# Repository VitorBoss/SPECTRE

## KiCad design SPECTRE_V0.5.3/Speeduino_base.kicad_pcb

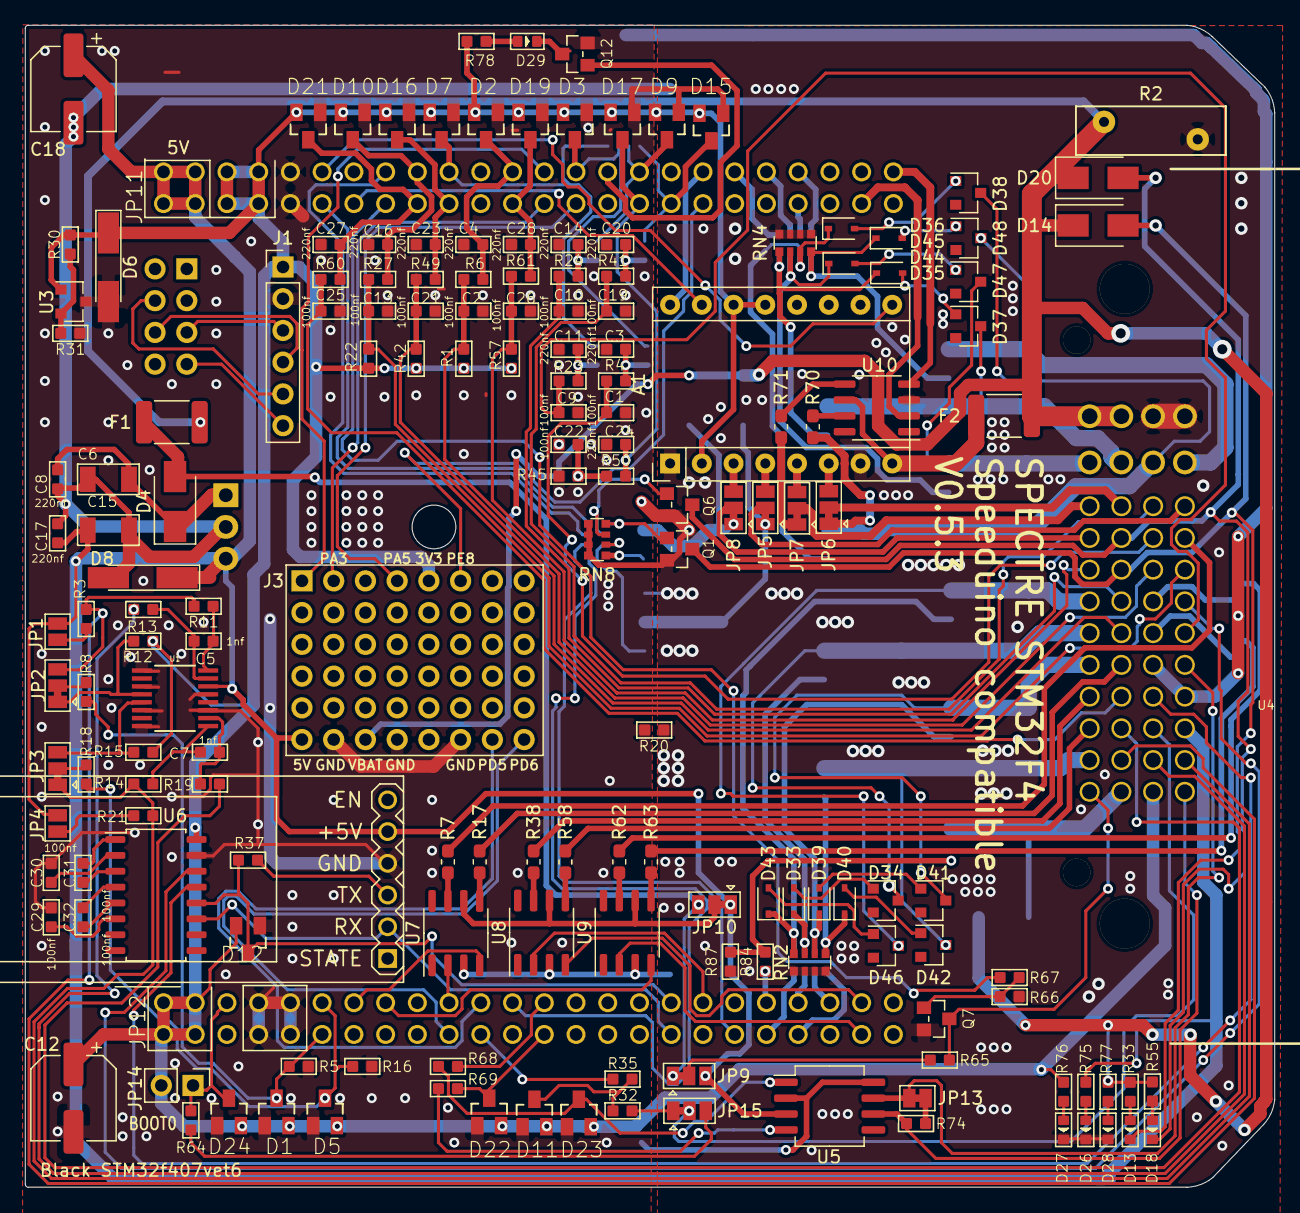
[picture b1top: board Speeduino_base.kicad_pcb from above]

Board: 2 copper layers, 100.0 x 93.0 mm, 197 parts (0 on the bottom side), 180 nets.

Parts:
A1: Pololu_Breakout_DRV8825; Pololu_Breakout-16_15.2x20.3mm
C1, C2, C9, C10, C13, C19, C21, C22, C25, C26, C29, C30, C31, C32: 100nf; C0603
C3, C4, C8, C11, C14, C16, C17, C20, C23, C24, C27, C28: 220nf; C0603
C5, C7: 1nf; C0603
C6, C15: 10uf; C1206
C12, C18: 470uF 6.3V; CP_Elec_6.3x7.7
D1, D2, D3, D5, D7, D9, D10, D11, D12, D15, D16, D17, D19, D21, D22, D23, D24: BAT54S; SOT23
D4, D14, D20, D30, D31, D32: 1N4007; D_SMA
D6: Zener 3.6V; D_MiniMELF_Handsoldering
D8: Zener 5.1V; D_MiniMELF_Handsoldering
D13, D18, D26, D27, D28, D29: YEL; LED-0603
D33, D35, D36, D39, D40, D43, D44, D45: 1N4148WS; D_SOD-323
D34, D37, D38, D41, D42, D46, D47, D48: BZX84C39; D_SOT-23_ANK
F1, F2: PPTC 16V2A; R_1812_4532Metric_Pad1.30x3.40mm_HandSolder
J1: Conn_01x06_Male; PinHeader_1x06_P2.54mm_Vertical
J2: Conn_02x04_Odd_Even; PinHeader_2x04_P2.54mm_Vertical
J3: ProtoArea; Proto_area
JP1, JP4: Jumper_NO_Small; SolderJumper-2_P1.3mm_Open_Pad1.0x1.5mm
JP2, JP3, JP5, JP6, JP7, JP8, JP9, JP10, JP15, JP16, JP18: SolderJumper_3_Bridged12; SolderJumper-3_P1.3mm_Bridged12_Pad1.0x1.5mm
JP11, JP12: PINHD-2X24; 2X24
JP13: Jumper_NC_Small; SolderJumper-2_P1.3mm_Bridged_Pad1.0x1.5mm
JP14: Jumper_NO_Small; PinHeader_1x02_P2.54mm_Vertical
Q1, Q6, Q7, Q12: AO3400; SOT-23
Q10, Q11, Q13, Q14, Q15, Q16, Q17, Q18, Q19, Q20, Q21: BSP78; SOT223
R1, R22, R31, R42, R57: 2k49; R0603
R2: VARISTOR-18V; RV_Disc_D12mm_W3.9mm_P7.5mm
R3, R12, R15, R21, R32, R35, R65, R68, R69: 1k; R0603
R4, R6, R8, R18, R23, R24, R27, R33, R37, R41, R49, R50, R55, R60, R61, R64, R77: 470R; R0603
R5, R11, R13, R14, R16, R19: 10k; R0603
R7, R17, R38, R58, R62, R63, R70, R71: 10R; R_0603_1608Metric_Pad1.05x0.95mm_HandSolder
R9, R25, R28, R46: 4k7; R0603
R20: 0R0; R0603
R30: 1k8; R0603
R44: 33k; R0603
R45: 5k1; R0603
R66, R87: 10K; R0603
R67, R76, R78, R84: 100R; R0603
R74: 120R; R0603
R75: 220R; R0603
RN1, RN3, RN7: 100R; R_Array_Convex_4x0612
RN2, RN4, RN8: 10K; R_Array_Convex_4x0612
RN6: 9K1; R_Array_Convex_4x0612
U1: MAX9926UAEE+; 21-0055H_16
U2: LM78M05_TO220; TO-220-3_Horizontal_TabUp
U3: TL431DBZ; SOT-23
U4: molex_48pin; Molex_48
U5: TJA1050; SO-8_5.3x6.2mm_P1.27mm
U6: MAX3232; SOIC-16_4.55x10.3mm_P1.27mm
U7, U8, U9, U10: MIC4427; SO-8_3.9x4.9mm_P1.27mm
U$1: WIRELESS-BLUETOOTH-HC-05

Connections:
3.3V: A1.2, A1.13, A1.14, C12.1, D1.2, D2.2, D3.2, D5.2, D6.1, D7.2, D9.2, D10.2, D11.2, D12.2, D15.2, D16.2, D17.2, D19.2, D21.2, D22.2, D23.2, D24.2, J1.1, J3.5, JP11.5, JP11.6, JP11.7, JP11.8, JP12.1, JP12.2, JP12.3, JP12.4, JP14.2, R1.2, R12.2, R15.2, R22.2, R30.1, R42.2, R57.2, R76.2, R78.2, U3.1, U4.46, U6.16
5V: C15.2, C17.2, C18.1, D8.1, J3.41, JP1.2, JP4.2, JP9.3, JP10.1, JP11.1, JP11.2, JP11.3, JP11.4, R75.2, U1.14, U2.3, U4.37, U5.3, U$1.5
/BT_TX: R37.2, U$1.3
AIN_1: C2.2, R1.1, R6.1, U4.18
AIN_2: C1.2, R4.1, U4.14
AIN_3: C26.2, R57.1, R61.1, U4.20
BARO: C19.2, R41.1, U4.10
BME280_CS: J1.5, J2.4
BOOST-OUT: D30.2, Q16.2, Q16.4, U4.47
BOOT0: D24.3, JP12.5, JP14.1, R64.1
BOOT0_EXT: JP15.3, R64.2
CANH: JP13.2, U4.29, U5.7
CANL: R74.1, U4.45, U5.6
CLT: C21.2, R42.1, R49.1, U4.27
FAN: D18.-, D20.2, Q6.3, U4.15
FLEX_FUEL_IN: JP15.1, R32.2
FUEL_PUMP: D13.-, D14.2, Q1.3, U4.19
GND: C1.1, C2.1, C3.1, C4.1, C9.1, C10.1, C11.1, C12.2, C13.1, C14.1, C16.1, C19.1, C20.1, C21.1, C22.1, C23.1, C24.1, C25.1, C26.1, C27.1, C28.1, C29.2, C30.2, D1.1, D2.1, D3.1, D5.1, D6.2, D7.1, D9.1, D10.1, D11.1, D12.1, D15.1, D16.1, D17.1, D19.1, D21.1, D22.1, D23.1, D24.1, J1.2, J3.42, J3.44, J3.46, JP11.9, JP11.10, JP12.7, JP12.8, JP12.9, JP12.10, JP16.1, JP18.1, Q12.2, R5.2, R16.2, R20.1, R31.2, R45.1, RN6.1, RN6.2, RN6.3, RN6.4, U1.1, U1.3, U1.6, U1.8, U1.11, U1.13, U3.3, U4.30, U4.33, U5.2, U5.8, U6.15, U$1.4
IAT: C13.2, R22.1, R27.1, U4.17
IDLE1-OUT: D31.2, JP5.1, Q17.2, Q17.4
IDLE2-OUT: D32.2, JP8.1, Q15.2, Q15.4
IGN1-OUT: R7.1, U4.13
IGN2-OUT: R17.1, U4.31
IGN3-OUT: R38.1, U4.36
IGN4-OUT: R58.1, U4.40
IGN5-OUT: JP18.3, R62.1
IGN6-OUT: JP16.3, R63.1
INJ1-OUT: D41.1, Q13.2, Q13.4, U4.32
INJ2-OUT: D42.1, Q14.2, Q14.4, U4.44
INJ3-OUT: D34.1, Q18.2, Q18.4, U4.28
INJ4-OUT: D46.1, Q19.2, Q19.4, U4.24
INJ5-OUT: D37.1, Q10.2, Q10.4, U4.7
INJ6-OUT: D47.1, Q20.2, Q20.4, U4.8
INJ7-OUT: D38.1, Q11.2, Q11.4, U4.6
INJ8-OUT: D48.1, Q21.2, Q21.4, U4.5
MAP: C9.2, R23.1, U4.25
unnamed: C3.2, R4.2, R9.1
unnamed: C5.1, R13.2, U1.15
unnamed: C5.2, R11.2, U1.16
unnamed: C6.2, C8.2, D4.1, U2.1
unnamed: C7.1, R19.2, U1.10
unnamed: C7.2, R14.2, U1.9
unnamed: C11.2, R23.2, R25.1
unnamed: C14.2, R24.2, R28.1
unnamed: C20.2, R41.2, R46.1
unnamed: C22.2, R44.1, R45.2, R50.1
unnamed: C29.1, U6.6
unnamed: C30.1, U6.2
unnamed: C31.1, U6.1
unnamed: C31.2, U6.3
unnamed: C32.1, U6.4
unnamed: C32.2, U6.5
unnamed: D11.3, R32.1, R35.2
unnamed: D13.+, R33.1
unnamed: D18.+, R55.1
unnamed: D23.3, R68.2, U5.1
unnamed: D26.+, R75.1
unnamed: D27.+, R76.1
unnamed: D28.+, R77.1
unnamed: D29.+, R78.1
unnamed: D29.-, Q12.3
unnamed: D33.1, Q18.1, RN1.6, RN2.3
unnamed: D33.2, D34.2
unnamed: D35.1, Q10.1, RN3.8, RN4.1
unnamed: D35.2, D37.2
unnamed: D36.1, Q11.1, RN3.6, RN4.3
unnamed: D36.2, D38.2
unnamed: D39.1, Q13.1, RN1.7, RN2.2
unnamed: D39.2, D41.2
unnamed: D40.1, Q14.1, RN1.8, RN2.1
unnamed: D40.2, D42.2
unnamed: D43.1, Q19.1, RN1.5, RN2.4
unnamed: D43.2, D46.2
unnamed: D44.1, Q20.1, RN3.7, RN4.2
unnamed: D44.2, D47.2
unnamed: D45.1, Q21.1, RN3.5, RN4.4
unnamed: D45.2, D48.2
unnamed: JP1.1, R3.2
unnamed: JP2.1, R12.1, U1.4
unnamed: JP2.2, R8.2
unnamed: JP3.2, R18.2
unnamed: JP3.3, R15.1, U1.5
unnamed: JP4.1, R21.2
unnamed: JP5.2, U4.9
unnamed: JP6.2, U4.11
unnamed: JP7.2, U4.12
unnamed: JP8.2, U4.16
unnamed: JP9.2, R65.2
unnamed: JP10.2, U7.6, U8.6, U9.6
unnamed: JP13.1, R74.2
unnamed: JP15.2, U4.38
unnamed: JP16.2, U4.26
unnamed: JP18.2, U4.22
unnamed: Q1.1, RN7.1, RN8.4
unnamed: Q6.1, RN7.2, RN8.3
unnamed: Q7.1, R66.2, R67.2
unnamed: Q15.1, RN7.4, RN8.1
unnamed: Q16.1, R84.2, R87.2
unnamed: Q17.1, RN7.3, RN8.2
unnamed: R7.2, U7.7
unnamed: R17.2, U7.5
unnamed: R30.2, R31.1, U3.2
unnamed: R38.2, U8.7
unnamed: R58.2, U8.5
unnamed: R62.2, U9.7
unnamed: R63.2, U9.5
unnamed: R69.2, U5.4
unnamed: R70.2, U10.7
unnamed: R71.2, U10.5
O2: C10.2, R24.1, U4.23
PA0: C4.2, D2.3, JP11.23, R6.2
PA1: C28.2, D19.3, JP11.24, R61.2
PA2: J3.1, JP11.25
PA3: J3.2, JP11.26
PA4: D3.3, JP11.27, R9.2, RN6.7
PA5: J3.4, JP11.28
PA6: JP11.29, Q12.1
PA8: JP12.35, U8.2
PA9: JP12.34, U6.11, U$1.2
PA10: D12.3, JP12.33, R37.1, U6.12
PB1: D15.3, JP11.34, R46.2, RN6.5
PB7: JP12.15, U9.4
PB9: JP12.13, U7.4
PB12: JP11.46, U10.2
PB13: JP11.47, U10.4
PC0: C16.2, D10.3, JP11.17, R27.2
PC1: C27.2, D21.3, JP11.18, R60.2
PC2: D7.3, JP11.19, R25.2, RN6.8
PC3: C23.2, D16.3, JP11.20, R49.2
PC4: D9.3, JP11.31, R28.2, RN6.6
PC5: C24.2, D17.3, JP11.32, R50.2
PC6: JP12.39, R84.1
PC7: JP12.38, RN7.6
PC13: JP11.16, R67.1
PD0: D22.3, JP12.26, R69.1
PD1: JP12.25, R68.1
PD3: JP12.23, RN7.5
PD4: JP12.22, R35.1
PD5: J3.47, JP12.21
PD6: J3.48, JP12.20
PD7: JP12.19, U7.2
PD9: JP12.46, U9.2
PD10: JP12.45, U8.4
PD12: JP12.43, RN1.2
PD13: JP12.42, RN1.1
PD14: JP12.41, RN1.3
PD15: JP12.40, RN1.4
PE0: D1.3, JP12.12, R5.1, R8.1
PE1: D5.3, JP12.11, R16.1, R18.1
PE2: A1.9, JP11.11
PE3: JP11.12, RN7.8
PE5: A1.15, JP11.14
PE6: JP11.15, RN7.7
PE7: A1.16, JP11.35
PE8: J3.6, JP11.36
PE9: JP11.37, RN3.1
PE11: JP11.39, RN3.2
PE13: JP11.41, RN3.4
PE14: JP11.42, RN3.3
PWR_GND: A1.1, A1.7, C6.1, C8.1, C15.1, C17.1, C18.2, D8.2, D26.-, D27.-, D28.-, Q1.2, Q6.2, Q7.2, Q10.3, Q11.3, Q13.3, Q14.3, Q15.3, Q16.3, Q17.3, Q18.3, Q19.3, Q20.3, Q21.3, R2.1, R20.2, R66.1, R87.1, RN2.5, RN2.6, RN2.7, RN2.8, RN4.5, RN4.6, RN4.7, RN4.8, RN8.5, RN8.6, RN8.7, RN8.8, U2.2, U4.1, U4.2, U7.3, U8.3, U9.3, U10.3
RS232_RX: U4.34, U6.13
RS232_TX: U4.21, U6.14
SPI1_MISO: J1.6, J2.7
SPI1_MOSI: J1.4, J2.6
SPI1_SCK: J1.3, J2.5
STEP_1A_OUT: A1.4, JP5.3
STEP_1B_OUT: A1.5, JP7.3
STEP_2A_OUT: A1.3, JP8.3
STEP_2B_OUT: A1.6, JP6.3
Spare_1-Out: JP7.1, R71.1
Spare_2-Out: JP6.1, R70.1
TACHO-OUT: Q7.3, R65.1, U4.48
TPS: C25.2, R60.1, U4.35
VBAT: D14.1, D20.1, D30.1, D31.1, D32.1, F1.1, F2.1, J3.43, R2.2, R33.2, R44.2, R55.2, R77.2, U4.3, U4.4
VBAT_F1: D4.2, F1.2, JP9.1, JP10.3
VR1+: JP2.3, R3.1, R11.1, U4.43
VR1-: R13.1, U4.42
VR2+: JP3.1, R14.1, R21.1, U4.41
VR2-: R19.1, U4.39
V_IDLE: A1.8, F2.2, U10.6

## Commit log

2021-01-27 Increased VBAT width
2024-03-21 Minor changes
